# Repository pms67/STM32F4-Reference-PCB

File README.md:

# STM32F4-Reference-PCB
 KiCad + STM32F4 + USB + Buck converter video reference/test PCB.

- Learn how to design your own STM32-based PCB ([https://youtu.be/x_5rYfAyqq0](https://youtu.be/x_5rYfAyqq0))!
- Learn how to write firmware for the STM32 microcontroller ([https://youtu.be/C7-8nUU6e3E](https://youtu.be/C7-8nUU6e3E))!

You can order this board (incl. SMT assembly) at [https://www.jlcpcb.com](https://www.jlcpcb.com). Gerber and assembly files are in the relevant repo folders.

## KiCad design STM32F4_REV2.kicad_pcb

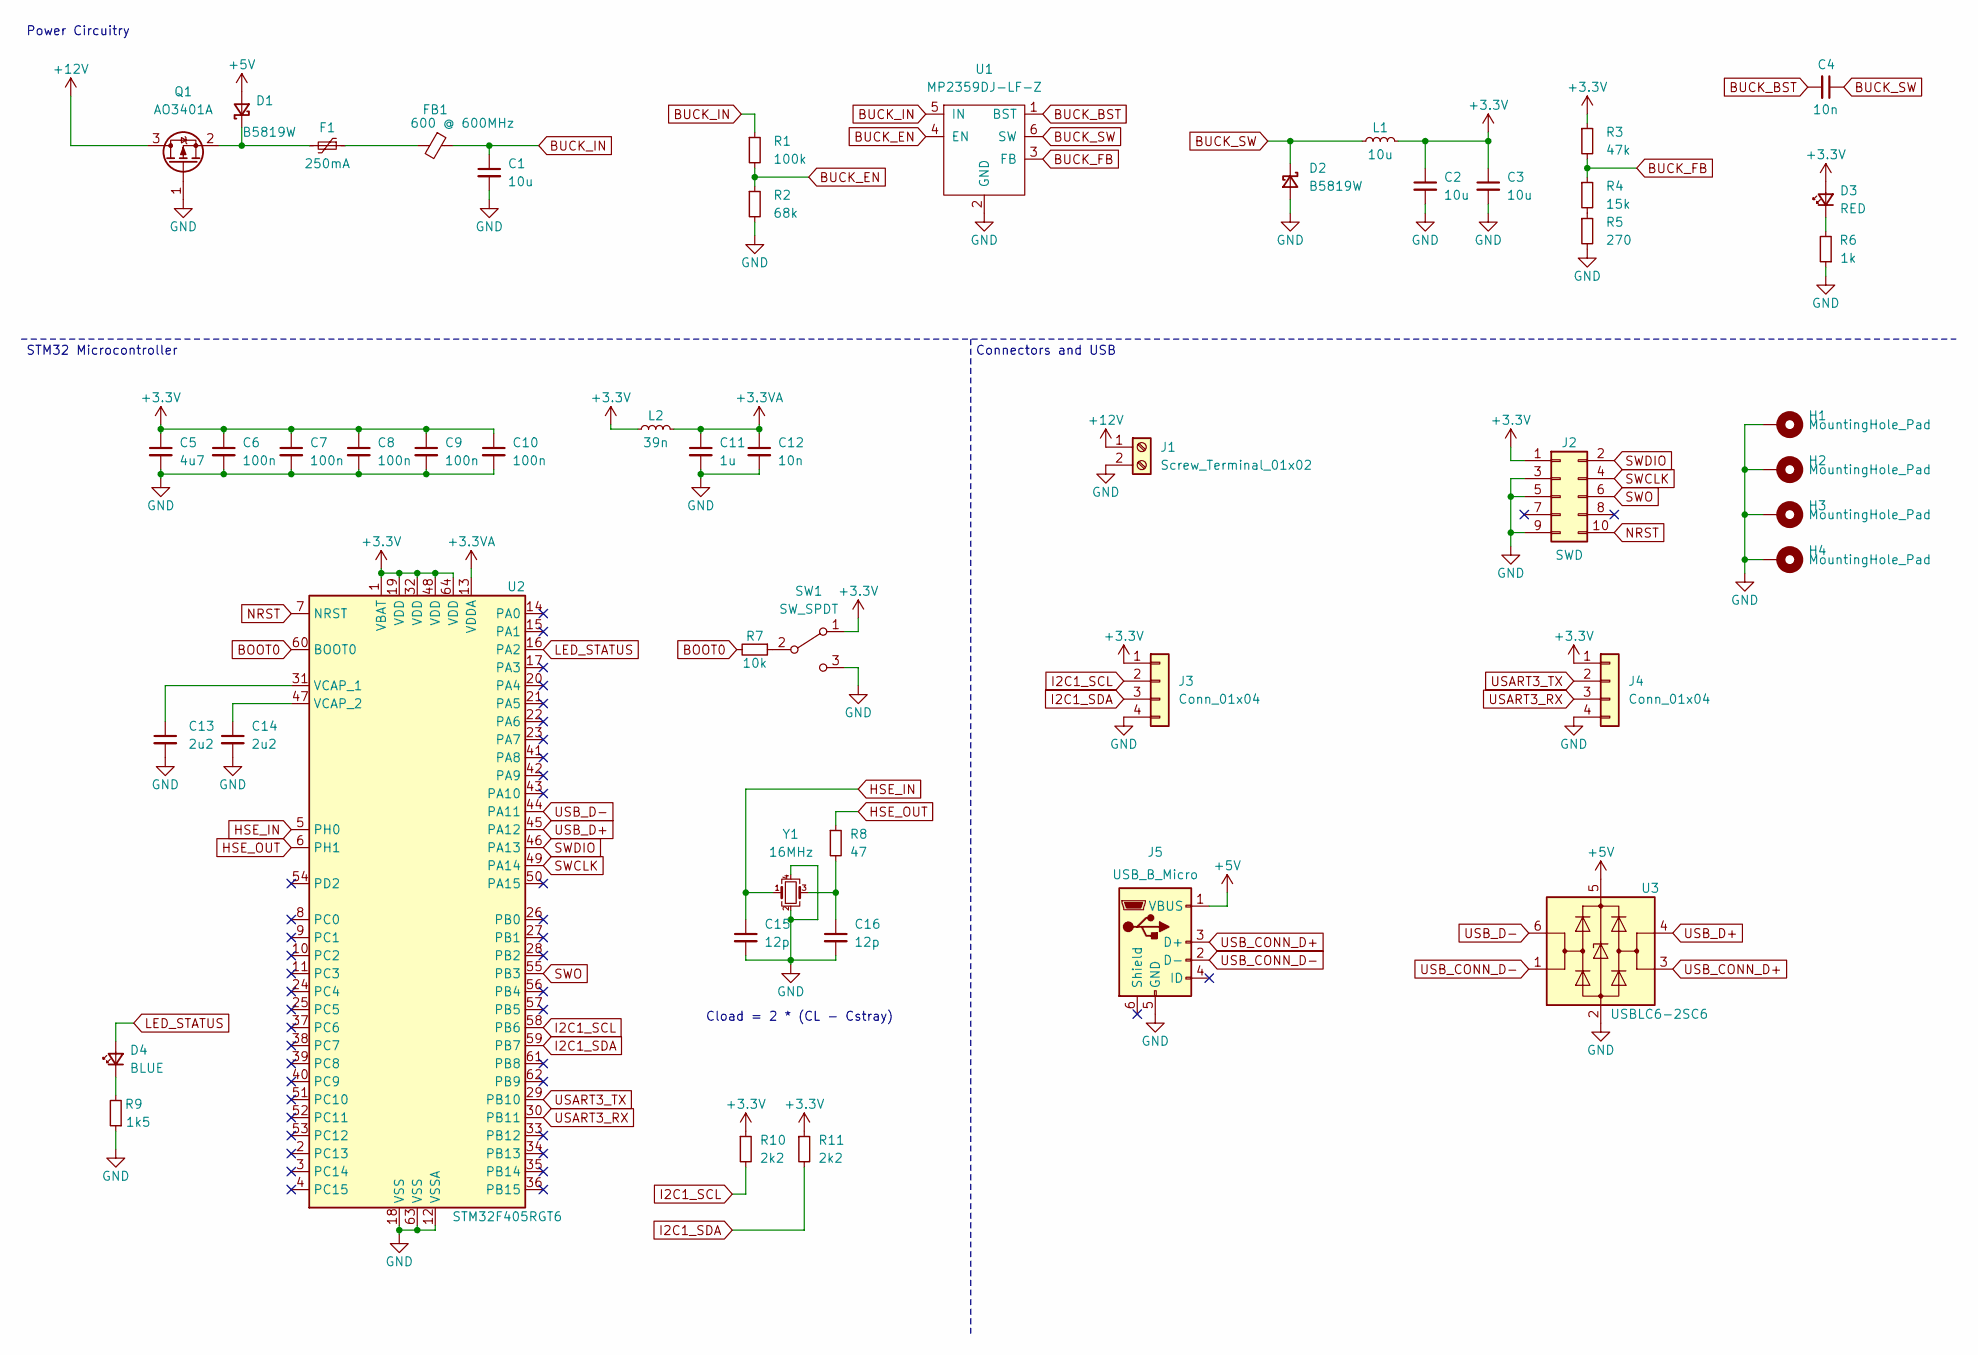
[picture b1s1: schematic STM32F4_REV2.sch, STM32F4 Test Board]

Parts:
C1, C2, C3: 10u; C_1206_3216Metric; LCSC Part # C13585
C4: 10n; C_0603_1608Metric; LCSC Part # C57112
C5: 4u7; C_0603_1608Metric; LCSC Part # C19666
C6, C7, C8, C9, C10: 100n; C_0402_1005Metric; LCSC Part # C1525
C11: 1u; C_0402_1005Metric; LCSC Part # C52923
C12: 10n; C_0402_1005Metric; LCSC Part # C15195
C13, C14: 2u2; C_0603_1608Metric; LCSC Part # C23630
C15, C16: 12p; C_0402_1005Metric; LCSC Part # C1547
D1, D2: B5819W; D_SOD-123; LCSC Part # C8598
D3: RED; LED_0603_1608Metric; LCSC Part # C2286
D4: BLUE; LED_0603_1608Metric; LCSC Part # C72041
F1: 250mA; Fuse_1206_3216Metric; LCSC Part # C369159
FB1: 600 @ 600MHz; L_0805_2012Metric; LCSC Part # C1017
H1, H2, H3, H4: MountingHole_Pad; MountingHole_4.3mm_M4_Pad_Via
J1: Screw_Terminal_01x02; TerminalBlock_Phoenix_PT-1,5-2-3.5-H_1x02_P3.50mm_Horizontal
J2: SWD; PinHeader_2x05_P1.27mm_Vertical_SMD
J3, J4: Conn_01x04; Molex_PicoBlade_53048-0410_1x04_P1.25mm_Horizontal
J5: USB_B_Micro; USB_MICRO_B_101181930001LF
L1: 10u; L_Sunlord_MWSA0518_5.4x5.2mm; LCSC Part # C139506
L2: 39n; L_0402_1005Metric; LCSC Part # C26443
Q1: AO3401A; SOT-23; LCSC Part # C15127
R1: 100k; R_0603_1608Metric; LCSC Part # C25803
R2: 68k; R_0603_1608Metric; LCSC Part # C23231
R3: 47k; R_0603_1608Metric; LCSC Part # C25819
R4: 15k; R_0603_1608Metric; LCSC Part # C22809
R5: 270; R_0603_1608Metric; LCSC Part # C22966
R6: 1k; R_0603_1608Metric; LCSC Part # C21190
R7: 10k; R_0402_1005Metric; LCSC Part # C25744
R8: 47; R_0402_1005Metric; LCSC Part # C25118
R9: 1k5; R_0603_1608Metric; LCSC Part # C22843
R10, R11: 2k2; R_0402_1005Metric; LCSC Part # C25879
SW1: SW_SPDT; SW_SPDT_PCM12
U1: MP2359DJ-LF-Z; SOT-23-6; LCSC Part # C14259
U2: STM32F405RGT6; LQFP-64_10x10mm_P0.5mm; LCSC Part # C15742
U3: USBLC6-2SC6; SOT-23-6; LCSC Part # C7519
Y1: 16MHz; Crystal_SMD_3225-4Pin_3.2x2.5mm; LCSC Part # C13738

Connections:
+3.3VA: C11.1, C12.1, L2.2, U2.13 (VDDA)
+3V3: C2.1, C3.1, C5.1, C6.1, C7.1, C8.1, C9.1, C10.1, D3.2 (A), J2.1, J3.1, J4.1, L1.2, L2.1, R3.1, R10.1, R11.1, SW1.1 (A), U2.1 (VBAT), U2.19 (VDD), U2.32 (VDD), U2.48 (VDD), U2.64 (VDD)
+5V: D1.2 (A), J5.1 (VBUS), U3.5 (VBUS)
+12V: J1.1, Q1.3 (D)
BOOT0: R7.2, U2.60 (BOOT0)
BUCK_BST: C4.2, U1.1 (BST)
BUCK_EN: R1.2, R2.1, U1.4 (EN)
BUCK_FB: R3.2, R4.1, U1.3 (FB)
BUCK_IN: C1.1, FB1.1, R1.1, U1.5 (IN)
BUCK_SW: C4.1, D2.1 (K), L1.1, U1.6 (SW)
GND: C1.2, C2.2, C3.2, C5.2, C6.2, C7.2, C8.2, C9.2, C10.2, C11.2, C12.2, C13.2, C14.2, C15.2, C16.2, D2.2 (A), H1.1, H2.1, H3.1, H4.1, J1.2, J2.3, J2.5, J2.9, J3.4, J4.4, J5.5 (GND), Q1.1 (G), R2.2, R5.2, R6.1, R9.1, SW1.3 (C), U1.2 (GND), U2.12 (VSSA), U2.18 (VSS), U2.63 (VSS), U3.2 (GND), Y1.2, Y1.4
HSE_IN: C15.1, U2.5 (PH0), Y1.1
HSE_OUT: R8.1, U2.6 (PH1)
I2C1_SCL: J3.2, R10.2, U2.58 (PB6)
I2C1_SDA: J3.3, R11.2, U2.59 (PB7)
LED_STATUS: D4.2 (A), U2.16 (PA2)
NRST: J2.10, U2.7 (NRST)
unnamed: C13.1, U2.31 (VCAP_1)
unnamed: C14.1, U2.47 (VCAP_2)
unnamed: C16.1, R8.2, Y1.3
unnamed: D1.1 (K), F1.2, Q1.2 (S)
unnamed: D3.1 (K), R6.2
unnamed: D4.1 (K), R9.2
unnamed: F1.1, FB1.2
unnamed: R4.2, R5.1
unnamed: R7.1, SW1.2 (B)
SWCLK: J2.4, U2.49 (PA14)
SWDIO: J2.2, U2.46 (PA13)
SWO: J2.6, U2.55 (PB3)
USART3_RX: J4.3, U2.30 (PB11)
USART3_TX: J4.2, U2.29 (PB10)
USB_CONN_D+: J5.3 (D+), U3.3 (I/O2)
USB_CONN_D-: J5.2 (D-), U3.1 (I/O1)
USB_D+: U2.45 (PA12), U3.4 (I/O2)
USB_D-: U2.44 (PA11), U3.6 (I/O1)

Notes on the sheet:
Cload = 2 * (CL - Cstray)
STM32 Microcontroller
Power Circuitry
Connectors and USB

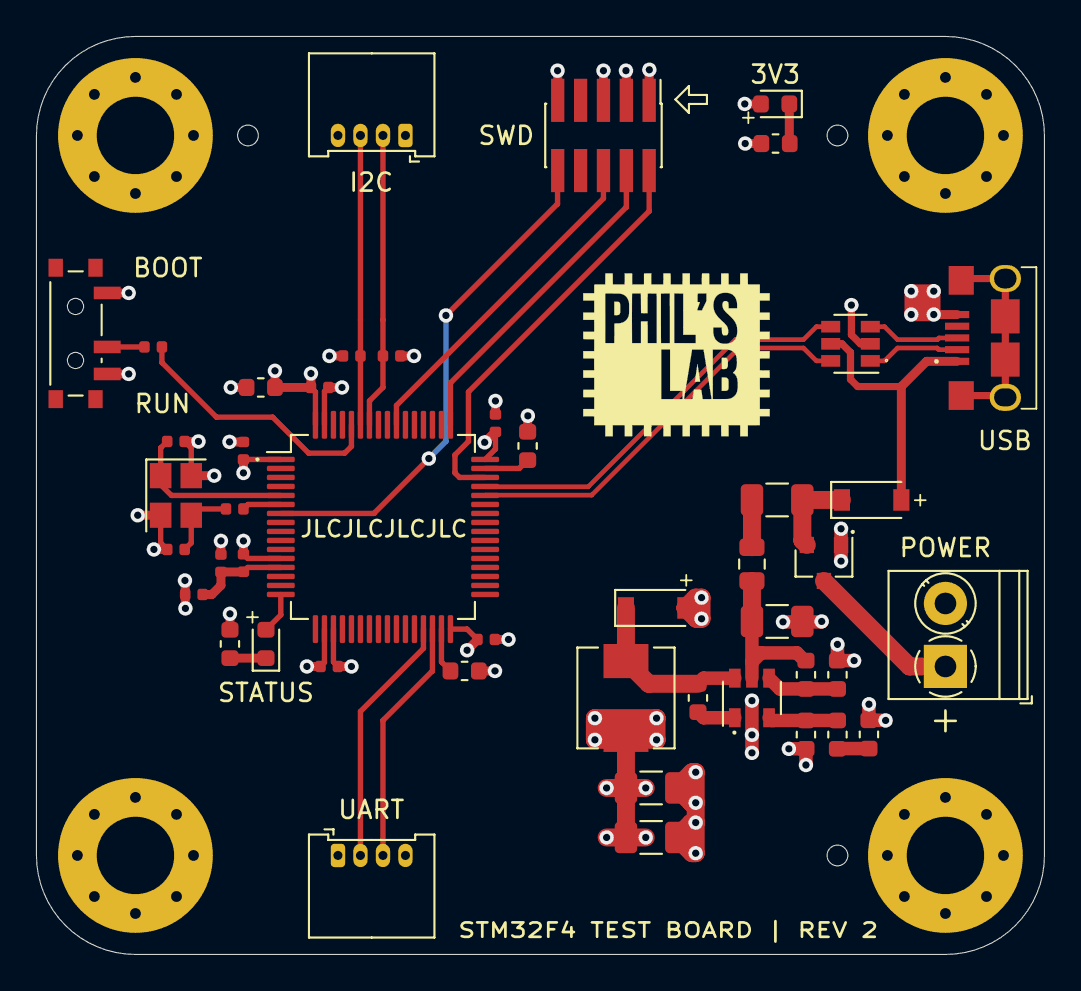
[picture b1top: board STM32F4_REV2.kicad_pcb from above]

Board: 4 copper layers, 56.0 x 51.0 mm, 50 parts (0 on the bottom side), 35 nets.

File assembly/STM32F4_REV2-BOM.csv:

Comment,Designator,Footprint,LCSC
"10u","C1,C2,C3","Capacitor_SMD:C_1206_3216Metric","C13585"
"1u","C11","Capacitor_SMD:C_0402_1005Metric","C52923"
"10n","C12","Capacitor_SMD:C_0402_1005Metric","C15195"
"2u2","C13,C14","Capacitor_SMD:C_0603_1608Metric","C23630"
"12p","C15,C16","Capacitor_SMD:C_0402_1005Metric","C1547"
"10n","C4","Capacitor_SMD:C_0603_1608Metric","C57112"
"4u7","C5","Capacitor_SMD:C_0603_1608Metric","C19666"
"100n","C6,C7,C8,C9,C10","Capacitor_SMD:C_0402_1005Metric","C1525"
"B5819W","D1,D2","Diode_SMD:D_SOD-123","C8598"
"RED","D3","LED_SMD:LED_0603_1608Metric","C2286"
"BLUE","D4","LED_SMD:LED_0603_1608Metric","C72041"
"250mA","F1","Fuse:Fuse_1206_3216Metric","C369159"
"600 @ 600MHz","FB1","Inductor_SMD:L_0805_2012Metric","C1017"
"MountingHole_Pad","H1,H2,H3,H4","MountingHole:MountingHole_4.3mm_M4_Pad_Via",""
"Screw_Terminal_01x02","J1","TerminalBlock_Phoenix:TerminalBlock_Phoenix_PT-1,5-2-3.5-H_1x02_P3.50mm_Horizontal",""
"SWD","J2","Connector_PinHeader_1.27mm:PinHeader_2x05_P1.27mm_Vertical_SMD",""
"Conn_01x04","J3,J4","Connector_Molex:Molex_PicoBlade_53048-0410_1x04_P1.25mm_Horizontal",""
"USB_B_Micro","J5","SchmillipKiCADLibrary:USB_MICRO_B_101181930001LF",""
"10u","L1","Inductor_SMD:L_Sunlord_MWSA0518_5.4x5.2mm","C139506"
"39n","L2","Inductor_SMD:L_0402_1005Metric","C26443"
"AO3401A","Q1","Package_TO_SOT_SMD:SOT-23","C15127"
"100k","R1","Resistor_SMD:R_0603_1608Metric","C25803"
"2k2","R10,R11","Resistor_SMD:R_0402_1005Metric","C25879"
"68k","R2","Resistor_SMD:R_0603_1608Metric","C23231"
"47k","R3","Resistor_SMD:R_0603_1608Metric","C25819"
"15k","R4","Resistor_SMD:R_0603_1608Metric","C22809"
"270","R5","Resistor_SMD:R_0603_1608Metric","C22966"
"1k","R6","Resistor_SMD:R_0603_1608Metric","C21190"
"10k","R7","Resistor_SMD:R_0402_1005Metric","C25744"
"47","R8","Resistor_SMD:R_0402_1005Metric","C25118"
"1k5","R9","Resistor_SMD:R_0603_1608Metric","C22843"
"SW_SPDT","SW1","Button_Switch_SMD:SW_SPDT_PCM12",""
"MP2359DJ-LF-Z","U1","Package_TO_SOT_SMD:SOT-23-6","C14259"
"STM32F405RGT6","U2","Package_QFP:LQFP-64_10x10mm_P0.5mm","C15742"
"USBLC6-2SC6","U3","Package_TO_SOT_SMD:SOT-23-6","C7519"
"16MHz","Y1","Crystal:Crystal_SMD_3225-4Pin_3.2x2.5mm","C13738"

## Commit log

2020-09-26 Initial commit.
